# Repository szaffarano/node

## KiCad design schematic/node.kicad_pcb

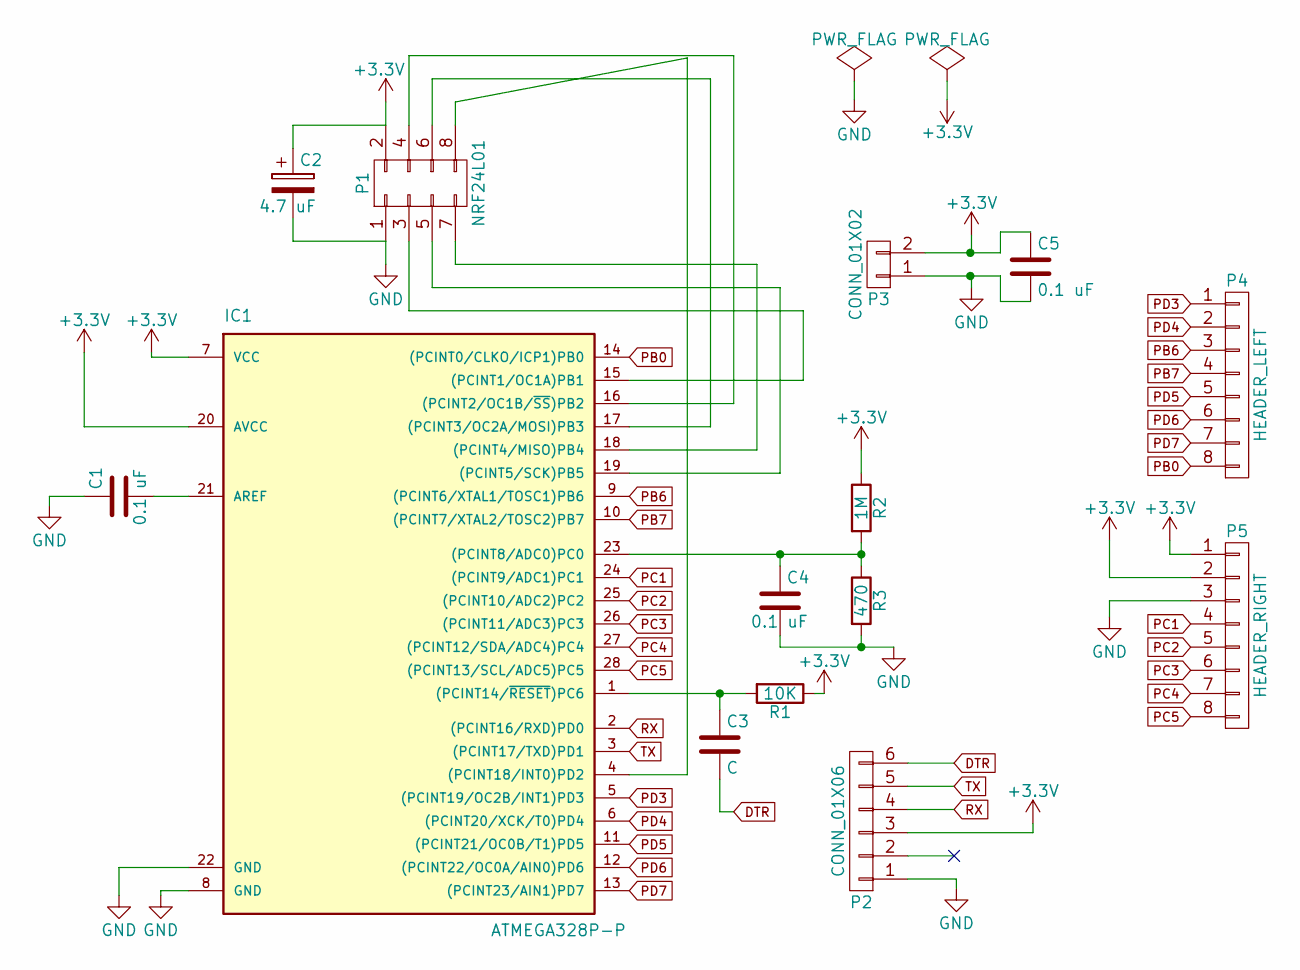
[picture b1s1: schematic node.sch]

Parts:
C1, C4, C5: 0.1 uF; C_Disc_D3_P2.5
C2: 4.7 uF; C_Radial_D5_L11_P2.5
C3: C; C_Disc_D3_P2.5
IC1: ATMEGA328P-P; DIP-28_W7.62mm
P1: NRF24L01; Socket_Strip_Straight_2x04
P2: CONN_01X06; Pin_Header_Straight_1x06
P3: CONN_01X02; Pin_Header_Straight_1x02
P4: HEADER_LEFT; Pin_Header_Straight_1x08
P5: HEADER_RIGHT; Pin_Header_Straight_1x08
R1: 10K; Resistor_Horizontal_RM10mm
R2: 1M; Resistor_Horizontal_RM10mm
R3: 470; Resistor_Horizontal_RM10mm

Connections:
+3V3: C2.1, C5.1, IC1.7 (VCC), IC1.20 (AVCC), P1.2, P2.3, P3.2, P5.1, P5.2, R1.1, R2.1
DTR: C3.2, P2.6
GND: C1.1, C2.2, C4.2, C5.2, IC1.8 (GND), IC1.22 (GND), P1.1, P2.1, P3.1, P5.3, R3.2
unnamed: C1.2, IC1.21 (AREF)
unnamed: C3.1, IC1.1 ((PCINT14/~RESET~)PC6), R1.2
unnamed: C4.1, IC1.23 ((PCINT8/ADC0)PC0), R2.2, R3.1
unnamed: IC1.4 ((PCINT18/INT0)PD2), P1.8
unnamed: IC1.15 ((PCINT1/OC1A)PB1), P1.3
unnamed: IC1.16 ((PCINT2/OC1B/~SS~)PB2), P1.4
unnamed: IC1.17 ((PCINT3/OC2A/MOSI)PB3), P1.6
unnamed: IC1.18 ((PCINT4/MISO)PB4), P1.7
unnamed: IC1.19 ((PCINT5/SCK)PB5), P1.5
PB0: IC1.14 ((PCINT0/CLKO/ICP1)PB0), P4.8
PB6: IC1.9 ((PCINT6/XTAL1/TOSC1)PB6), P4.3
PB7: IC1.10 ((PCINT7/XTAL2/TOSC2)PB7), P4.4
PC1: IC1.24 ((PCINT9/ADC1)PC1), P5.4
PC2: IC1.25 ((PCINT10/ADC2)PC2), P5.5
PC3: IC1.26 ((PCINT11/ADC3)PC3), P5.6
PC4: IC1.27 ((PCINT12/SDA/ADC4)PC4), P5.7
PC5: IC1.28 ((PCINT13/SCL/ADC5)PC5), P5.8
PD3: IC1.5 ((PCINT19/OC2B/INT1)PD3), P4.1
PD4: IC1.6 ((PCINT20/XCK/T0)PD4), P4.2
PD5: IC1.11 ((PCINT21/OC0B/T1)PD5), P4.5
PD6: IC1.12 ((PCINT22/OC0A/AIN0)PD6), P4.6
PD7: IC1.13 ((PCINT23/AIN1)PD7), P4.7
RX: IC1.2 ((PCINT16/RXD)PD0), P2.4
TX: IC1.3 ((PCINT17/TXD)PD1), P2.5

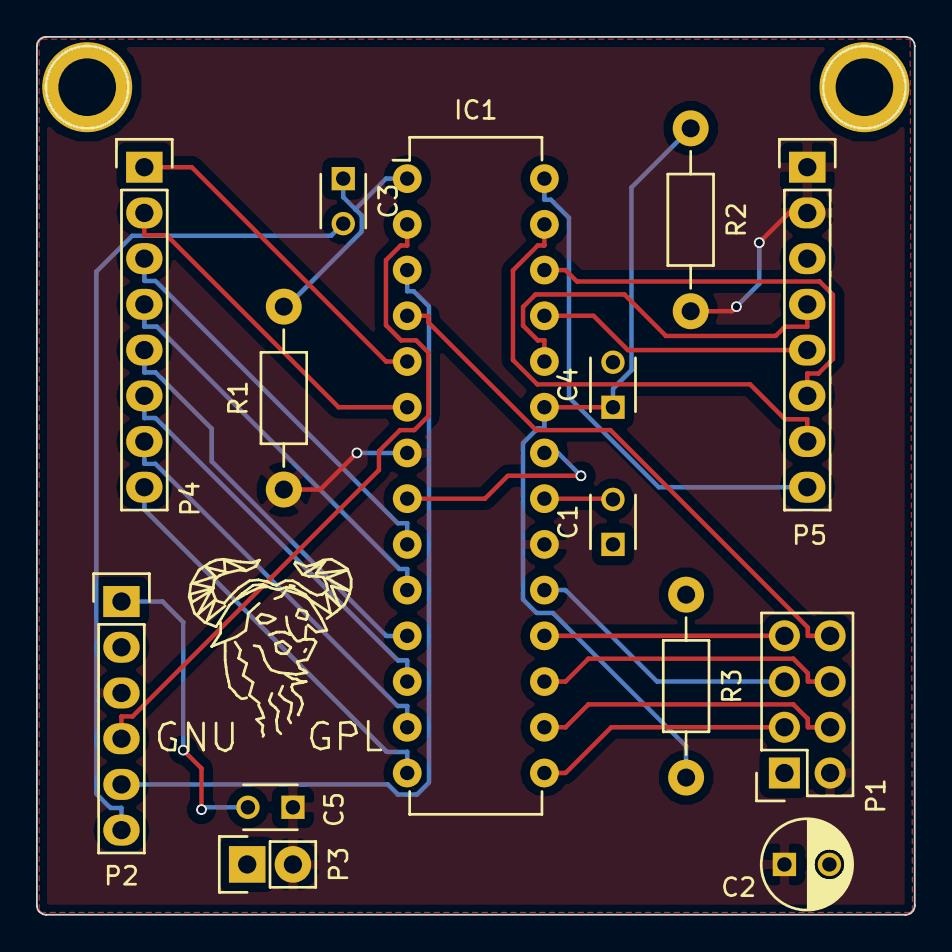
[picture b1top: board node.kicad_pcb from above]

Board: 2 copper layers, 48.8 x 48.8 mm, 17 parts (0 on the bottom side), 27 nets.

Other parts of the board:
REF1, REF2: 1pin
REF3: Symbol_GNU-Logo_SilkscreenTop

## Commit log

2015-12-31 inicial commit
2015-12-31 Add MySensors library
2016-01-02 Add batterylevel report and sleep mode
2016-01-03 quick & dirty
2016-01-04 add kicad design files
2016-01-04 new gerber files
2016-01-04 refactoring in pcb layout
2016-01-04 3d render
2016-01-04 add script helper
2016-01-05 change ftdi port
2016-01-05 new render image
2016-01-05 fix RF irq bug in schematic
